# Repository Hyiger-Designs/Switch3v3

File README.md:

Switch3v3  - A switching 3.3V regulator. Use as a drop-in replacement a standard 3-pin regulator.

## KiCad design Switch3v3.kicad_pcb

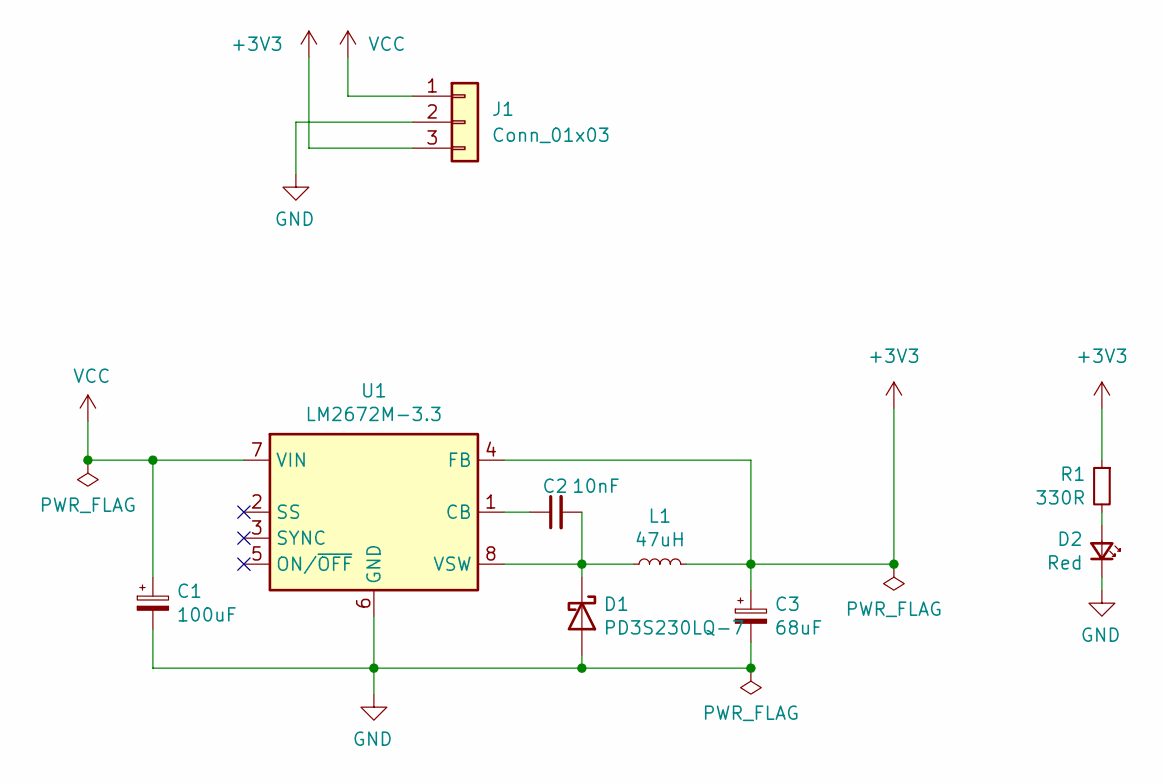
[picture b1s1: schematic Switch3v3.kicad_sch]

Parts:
C1: 100uF; CP_EIA-7343-43_Kemet-X; MPN T491X107M025AT
C2: 10nF; C_0603_1608Metric
C3: 68uF; CP_EIA-3216-18_Kemet-A; MPN T491A686K006AT
D1: PD3S230LQ-7; D_PowerDI-323; MPN PD3S230LQ-7
D2: Red; LED_0603_1608Metric
J1: Conn_01x03; PinHeader_1x03_P2.54mm_Horizontal
L1: 47uH; L_Coilcraft_LPS5030; MPN MSS6132-473MLC
R1: 330R; R_0603_1608Metric
U1: LM2672M-3.3; SOIC-8_3.9x4.9mm_P1.27mm; MPN LM2672M-3.3/NOPB

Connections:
+3V3: C3.1, J1.3, L1.2, R1.1, U1.4 (FB)
GND: C1.2, C3.2, D1.2 (A), D2.1 (K), J1.2, U1.6 (GND)
unnamed: C2.1, U1.1 (CB)
unnamed: C2.2, D1.1 (K), L1.1, U1.8 (VSW)
unnamed: D2.2 (A), R1.2
VCC: C1.1, J1.1, U1.7 (VIN)

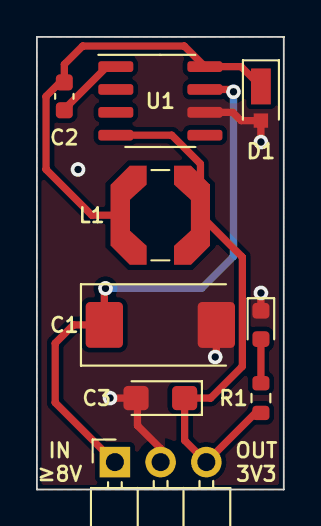
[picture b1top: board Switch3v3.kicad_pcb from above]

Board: 2 copper layers, 13.7 x 25.1 mm, 9 parts (0 on the bottom side), 6 nets.

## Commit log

2022-01-09 Initial version
